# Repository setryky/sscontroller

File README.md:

# SEGA Saturn Controller circuit

* Schematics originally drawn by Andre Biagioni based on inspection of an actual original controller and other sources of info found online (see thread at https://forum.fiozera.com.br/t/esquematico-de-controle-para-sega-saturn/111 - in Brazilian Portuguese)
* KICAD project drawn by Lucas de Souza (https://github.com/setryky)

This project is licensed under the MIT license.

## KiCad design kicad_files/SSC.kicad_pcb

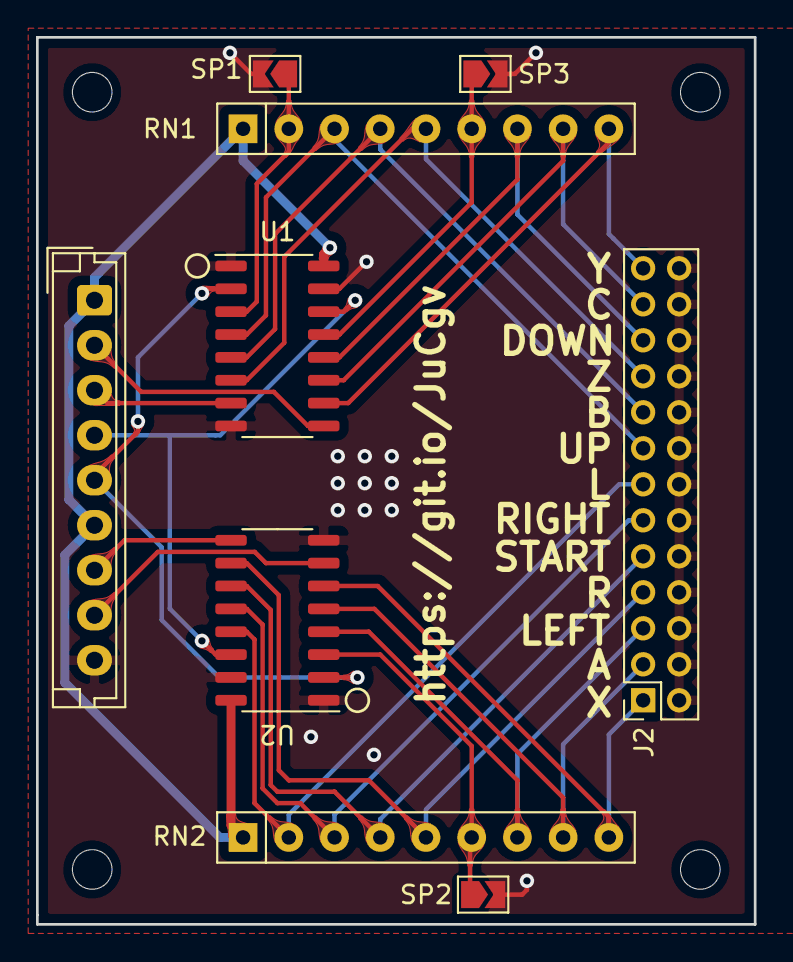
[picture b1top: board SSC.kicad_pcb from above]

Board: 2 copper layers, 39.9 x 49.3 mm, 9 parts (0 on the bottom side), 24 nets.

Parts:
J1: Conn_01x09; JST_EH_B9B-EH-A_1x09_P2.50mm_Vertical
J2: Conn_02x13_Top_Bottom; PinSocket_2x13_P2.00mm_Vertical
RN1, RN2: 10k; R_Array_SIP9
SP1, SP2, SP3: SolderJumper_2_Open; SolderJumper-2_P1.3mm_Open_TrianglePad1.0x1.5mm
U1, U2: 74LS153; SO-16_3.9x9.9mm_P1.27mm

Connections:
1C3: RN1.2, SP1.1, U1.3
2C3: RN2.6, SP2.1, U2.3
3C3: RN1.6, SP3.1, U1.13
A: J2.3, RN2.8, U2.5
B: J2.17, RN1.4, U1.5
C: J2.23, RN1.8, U1.11
D0: J1.3, U1.7
D1: J1.2, U1.9
D2: J1.8, U2.7
D3: J1.7, U2.9
DOWN: J2.21, RN1.7, U1.12
GND: J1.9, J2.2, J2.4, J2.6, J2.8, J2.10, J2.12, J2.14, J2.16, J2.18, J2.20, J2.22, J2.24, J2.26, SP1.2, SP2.2, SP3.2, U1.1, U1.8, U1.15, U2.1, U2.8, U2.15
L: J2.13, RN2.2, U2.13
LEFT: J2.5, RN2.7, U2.4
R: J2.7, RN2.5, U2.10
RIGHT: J2.11, RN2.3, U2.12
S0: J1.4, U1.14, U2.14
S1: J1.5, U1.2, U2.2
START: J2.9, RN2.4, U2.11
UP: J2.15, RN1.3, U1.4
VCC: J1.1, J1.6, RN1.1, RN2.1, U1.16, U2.16
X: J2.1, RN2.9, U2.6
Y: J2.25, RN1.9, U1.10
Z: J2.19, RN1.5, U1.6

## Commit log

2021-09-07 Os arquivos .zip e .rar são a mesma coisa
2021-09-08 Rearranging files on the repo
2021-09-08 Add files via upload
    Changed schematics a little and added holes to PCB.
2021-09-08 Delete SSC.pdf
    Deleted .pdf file on kicad_files folder.
2021-09-08 Delete SSC-Gerber.zip
    Deleted SSC-Gerber.zip to add it to gerbers folder.
2021-09-08 Added SSC-Gerber.zip file.
2021-09-08 Delete gerbers directory
    Removing clone files.
2021-09-08 Added THT version of PCB.
    THT version of the PCB, using the same schematics.
2021-09-08 Delete SSC-THT-Gerber directory
    changing the folder name.
2021-09-08 Delete SSC-THT directory
    same thing as last change
2021-09-08 Adding THT version of things again
2021-09-08 Higher resolution image
2026-03-04 Imagem
    Imagem para ajudar a soldar o cabo do controle na placa.
